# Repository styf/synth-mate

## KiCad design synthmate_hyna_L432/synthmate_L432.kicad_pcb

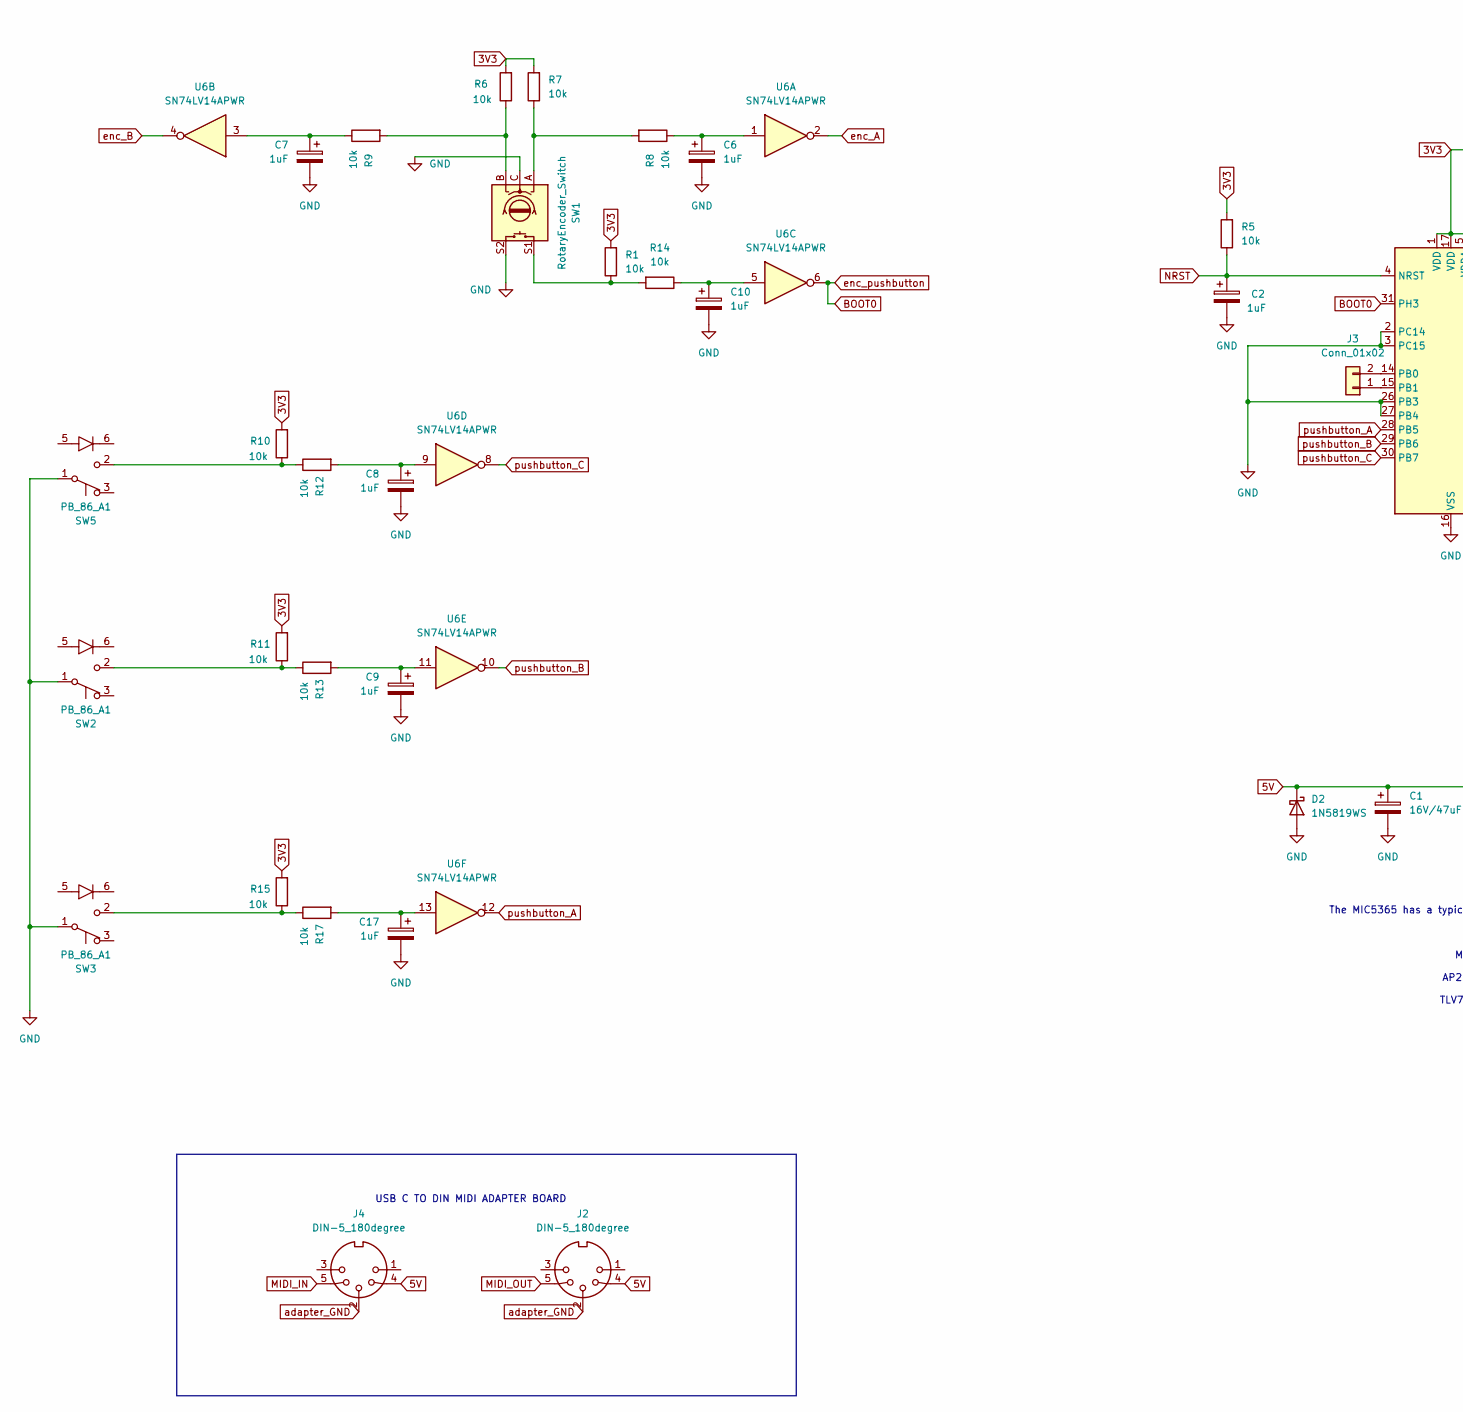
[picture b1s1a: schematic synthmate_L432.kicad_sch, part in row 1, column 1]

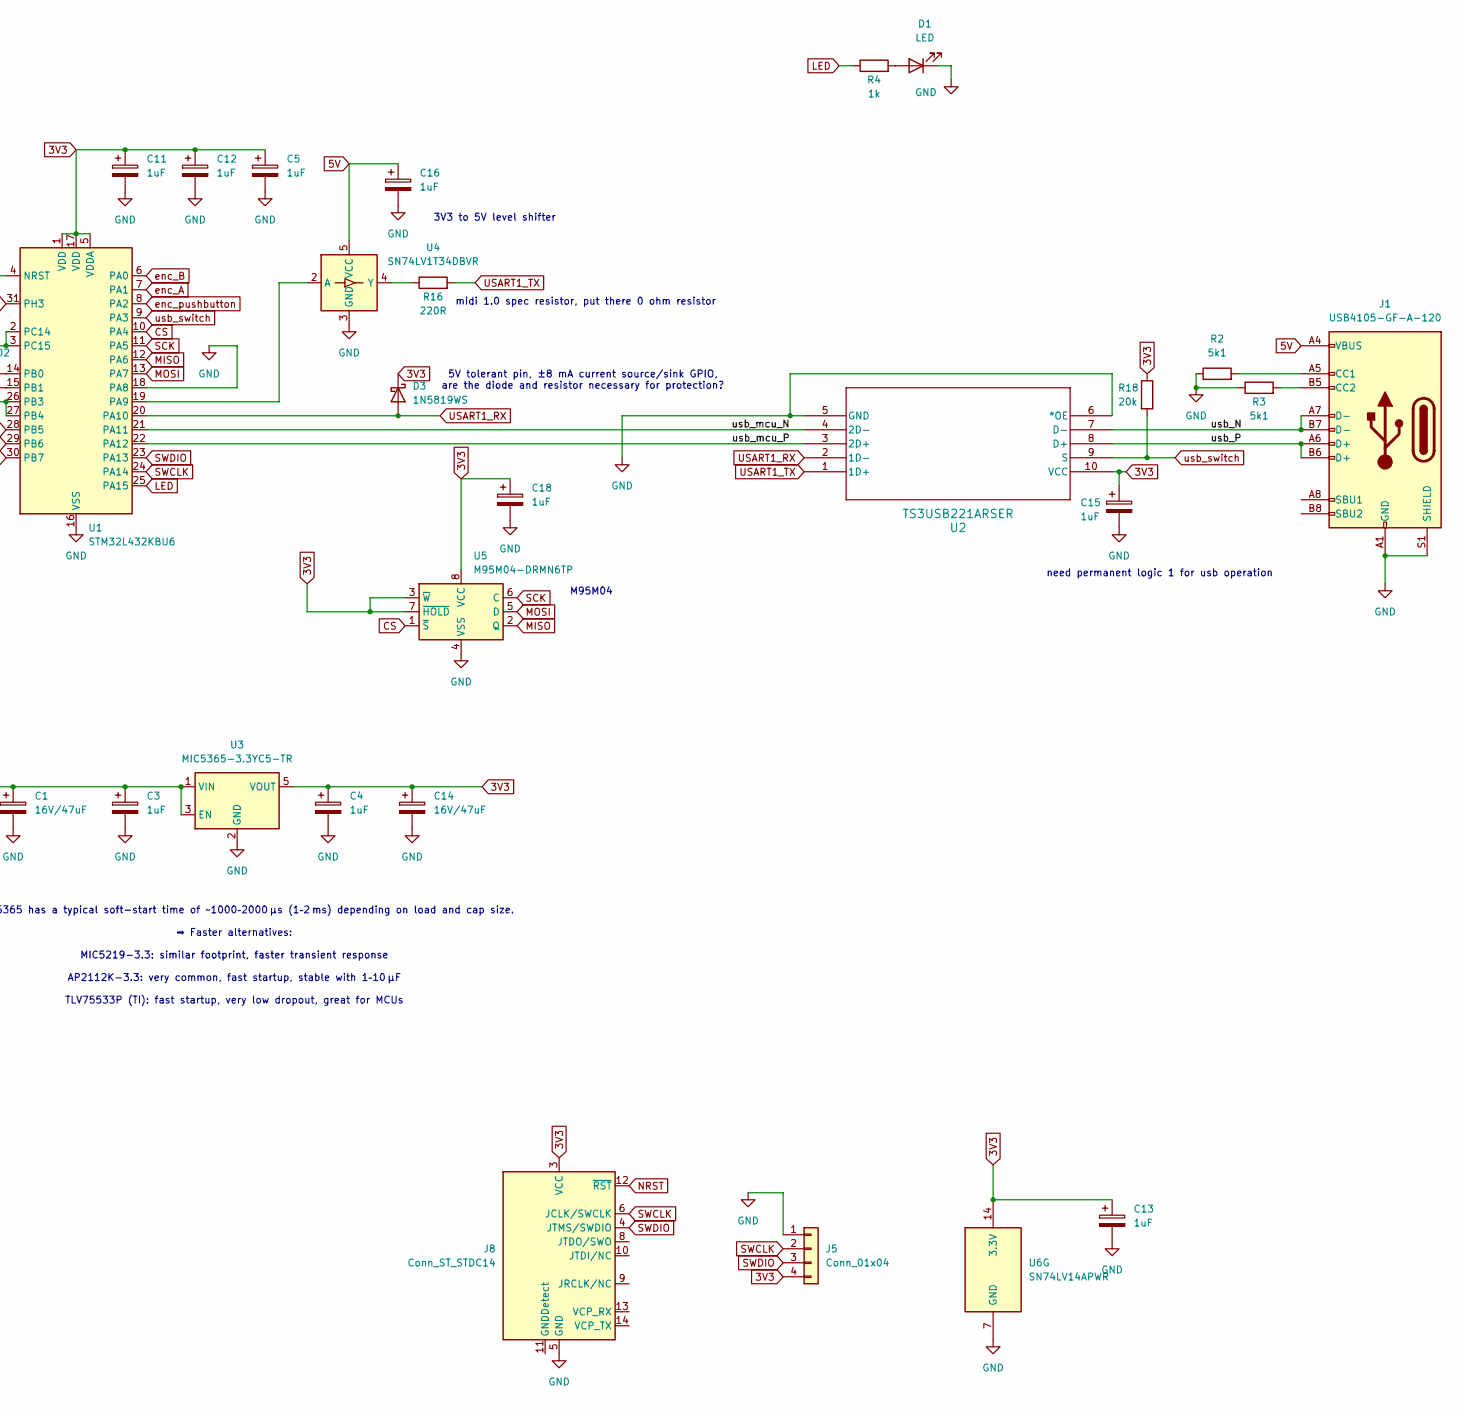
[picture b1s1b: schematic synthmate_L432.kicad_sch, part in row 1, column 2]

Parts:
C1, C14: 16V/47uF; C_1206_3216Metric
C2, C3, C4, C5, C6, C7, C8, C9, C10, C11, C12, C13, C15, C16, C17, C18: 1uF; C_0603_1608Metric
D1: LED; LED_0805_2012Metric_Pad1.15x1.40mm_HandSolder
D2, D3: 1N5819WS; D_SOD-323
J1: USB4105-GF-A-120; USB_C_Receptacle_GCT_USB4105-xx-A_16P_TopMnt_Horizontal
J2, J4: DIN-5_180degree
J3: Conn_01x02; PinHeader_1x02_P1.00mm_Vertical
J5: Conn_01x04; PinHeader_1x04_P2.54mm_Vertical
J8: Conn_ST_STDC14; PinHeader_2x07_P1.27mm_Vertical_SMD
R1, R5, R6, R7, R8, R9, R10, R11, R12, R13, R14, R15, R17: 10k; R_0603_1608Metric
R2, R3: 5k1; R_0603_1608Metric
R4: 1k; R_0603_1608Metric
R16: 220R; R_0603_1608Metric
R18: 20k; R_0603_1608Metric
SW1: RotaryEncoder_Switch; RotaryEncoder_Alps_EC11E-Switch_Vertical_H20mm
SW2, SW3, SW5: PB_86_A1; PB_86_A0
U1: STM32L432KBU6; QFN-32-1EP_5x5mm_P0.5mm_EP3.45x3.45mm
U2: TS3USB221ARSER; RSE10
U3: MIC5365-3.3YC5-TR; SOT-353_SC-70-5
U4: SN74LV1T34DBVR; SOT-23-5
U5: M95M04-DRMN6TP; SOIC-8_3.9x4.9mm_P1.27mm
U6: SN74LV14APWR; TSSOP-14_4.4x5mm_P0.65mm

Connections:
3V3: C4.1, C5.1, C11.1, C12.1, C13.1, C14.1, C15.1, C18.1, D3.1 (K), J5.4, J8.3 (VCC), R1.2, R5.2, R6.2, R7.2, R10.2, R11.2, R15.2, R18.1, U1.1 (VDD), U1.5 (VDDA), U1.17 (VDD), U2.10 (VCC), U3.5 (VOUT), U5.3 (~W), U5.7 (~HOLD), U5.8 (VCC), U6.14 (3.3V)
5V: C1.1, C3.1, C16.1, D2.1 (K), J1.A4 (VBUS), J1.A9 (VBUS), J1.B4 (VBUS), J1.B9 (VBUS), J2.4, J4.4, U3.1 (VIN), U3.3 (EN), U4.5 (VCC)
/usb_N: J1.A7 (D-), J1.B7 (D-), U2.7 (D-)
/usb_P: J1.A6 (D+), J1.B6 (D+), U2.8 (D+)
/usb_mcu_N: U1.21 (PA11), U2.4 (2D-)
/usb_mcu_P: U1.22 (PA12), U2.3 (2D+)
BOOT0: U1.8 (PA2), U1.31 (PH3), U6.6
CS: U1.10 (PA4), U5.1 (~S)
GND: C1.2, C2.2, C3.2, C4.2, C5.2, C6.2, C7.2, C8.2, C9.2, C10.2, C11.2, C12.2, C13.2, C14.2, C15.2, C16.2, C17.2, C18.2, D1.1 (K), D2.2 (A), J1.A1 (GND), J1.A12 (GND), J1.B1 (GND), J1.B12 (GND), J1.S1 (SHIELD), J5.1, J8.5 (GND), J8.7 (GND), R2.1, R3.1, SW1.C, SW1.S2, SW2.1 (B), SW3.1 (B), SW5.1 (B), U1.2 (PC14), U1.3 (PC15), U1.16 (VSS), U1.18 (PA8), U1.26 (PB3), U1.27 (PB4), U1.32 (VSS), U1.33 (VSS), U2.5 (GND), U2.6 (*OE), U3.2 (GND), U4.3 (GND), U5.4 (VSS), U6.7 (GND)
LED: R4.1, U1.25 (PA15)
MISO: U1.12 (PA6), U5.2 (Q)
MOSI: U1.13 (PA7), U5.5 (D)
NRST: C2.1, J8.12 (~RST), R5.1, U1.4 (NRST)
unnamed: C6.1, R8.1, U6.1
unnamed: C7.1, R9.1, U6.3
unnamed: C8.1, R12.2, U6.9
unnamed: C9.1, R13.2, U6.11
unnamed: C10.1, R14.1, U6.5
unnamed: C17.1, R17.2, U6.13
unnamed: D1.2 (A), R4.2
unnamed: J1.A5 (CC1), R2.2
unnamed: J1.B5 (CC2), R3.2
unnamed: J2.2, J4.2
unnamed: J3.1, U1.15 (PB1)
unnamed: J3.2, U1.14 (PB0)
unnamed: R1.1, R14.2, SW1.S1
unnamed: R6.1, R9.2, SW1.B
unnamed: R7.1, R8.2, SW1.A
unnamed: R11.1, R13.1, SW2.2 (C)
unnamed: R15.1, R17.1, SW3.2 (C)
unnamed: R10.1, R12.1, SW5.2 (C)
unnamed: U1.19 (PA9), U4.2 (A)
unnamed: R16.1, U4.4 (Y)
SCK: U1.11 (PA5), U5.6 (C)
SWCLK: J5.2, J8.6 (JCLK/SWCLK), U1.24 (PA14)
SWDIO: J5.3, J8.4 (JTMS/SWDIO), U1.23 (PA13)
USART1_RX: D3.2 (A), U1.20 (PA10), U2.2 (1D-)
USART1_TX: R16.2, U2.1 (1D+)
enc_A: U1.7 (PA1), U6.2
enc_B: U1.6 (PA0), U6.4
pushbutton_A: U1.28 (PB5), U6.12
pushbutton_B: U1.29 (PB6), U6.10
pushbutton_C: U1.30 (PB7), U6.8
usb_switch: R18.2, U1.9 (PA3), U2.9 (S)

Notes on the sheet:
The MIC5365 has a typical soft-start time of ~1000–2000 µs (1–2 ms) depending on load and cap size. ➡️ Faster alternatives: MIC5219-3.3: similar footprint, faster transient response AP2112K-3.3: very common, fast startup, stable with 1–10 µF TLV75533P (TI): fast startup, very low dropout, great for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
M95M04
5V tolerant pin, ±8 mA current source/sink GPIO, are the diode and resistor necessary for protection?
3V3 to 5V level shifter
need permanent logic 1 for usb operation
USB C TO DIN MIDI ADAPTER BOARD
midi 1.0 spec resistor, put there 0 ohm resistor

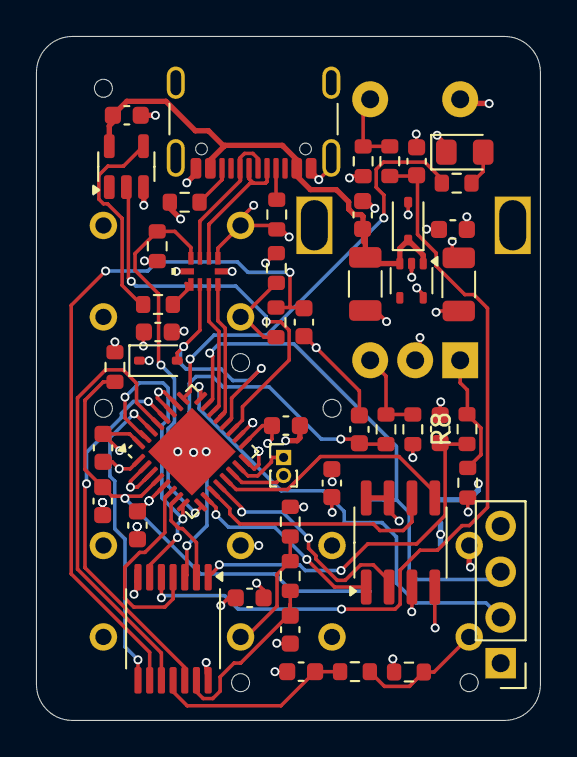
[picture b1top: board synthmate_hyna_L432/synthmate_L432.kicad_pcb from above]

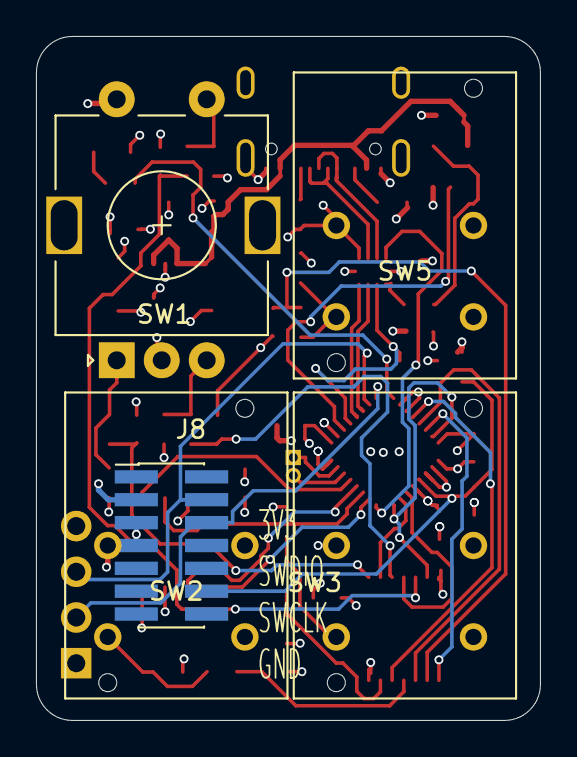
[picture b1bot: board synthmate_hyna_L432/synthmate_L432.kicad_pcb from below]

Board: 4 copper layers, 28.0 x 38.0 mm, 53 parts (5 on the bottom side), 43 nets.

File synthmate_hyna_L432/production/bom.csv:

Designator,Footprint,Quantity,Value,LCSC Part #
"C1, C14",1206,2,16V/47uF,
"C10, C11, C12, C13, C15, C16, C17, C18, C2, C3, C4, C5, C6, C7, C8, C9",0603,16,1uF,
D1,0805,1,LED,
"D2, D3",D_SOD-323,2,1N5819WS,
J1,USB_C_Receptacle_GCT_USB4105-xx-A_16P_TopMnt_Horizontal,1,USB4105-GF-A-120,
J3,PinHeader_1x02_P1.00mm_Vertical,1,Conn_01x02,
J5,PinHeader_1x04_P2.54mm_Vertical,1,Conn_01x04,
J8,PinHeader_2x07_P1.27mm_Vertical_SMD,1,Conn_ST_STDC14,
"R1, R10, R11, R12, R13, R14, R15, R17, R5, R6, R7, R8, R9",0603,13,10k,
R16,0603,1,220R,
R18,0603,1,20k,
"R2, R3",0603,2,5k1,
R4,0603,1,1k,
SW1,RotaryEncoder_Alps_EC11E-Switch_Vertical_H20mm,1,RotaryEncoder_Switch,
"SW2, SW3, SW5",PB_86_A0,3,PB_86_A1,
U1,QFN-32-1EP_5x5mm_P0.5mm_EP3.45x3.45mm,1,STM32L432KBU6,
U2,RSE10,1,TS3USB221ARSER,
U3,SOT-353_SC-70-5,1,MIC5365-3.3YC5-TR,
U4,SOT-23-5,1,SN74LV1T34DBVR,
U5,SOIC-8_3.9x4.9mm_P1.27mm,1,M95M04-DRMN6TP,
U6,TSSOP-14_4.4x5mm_P0.65mm,1,SN74LV14APWR,

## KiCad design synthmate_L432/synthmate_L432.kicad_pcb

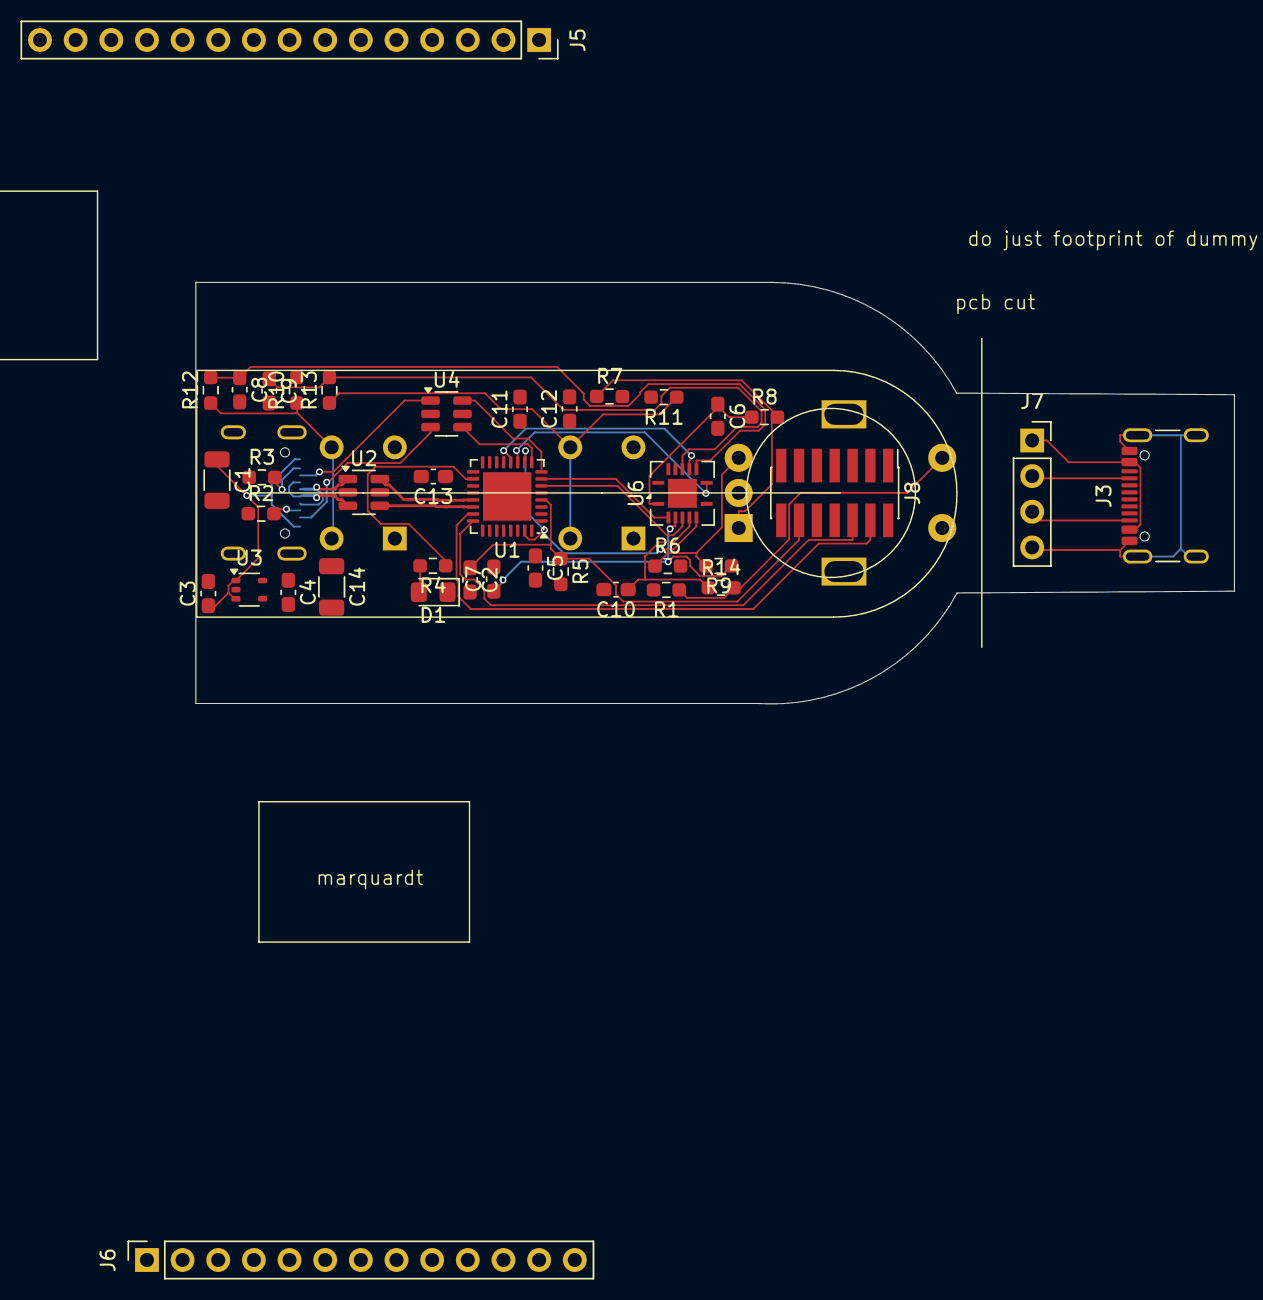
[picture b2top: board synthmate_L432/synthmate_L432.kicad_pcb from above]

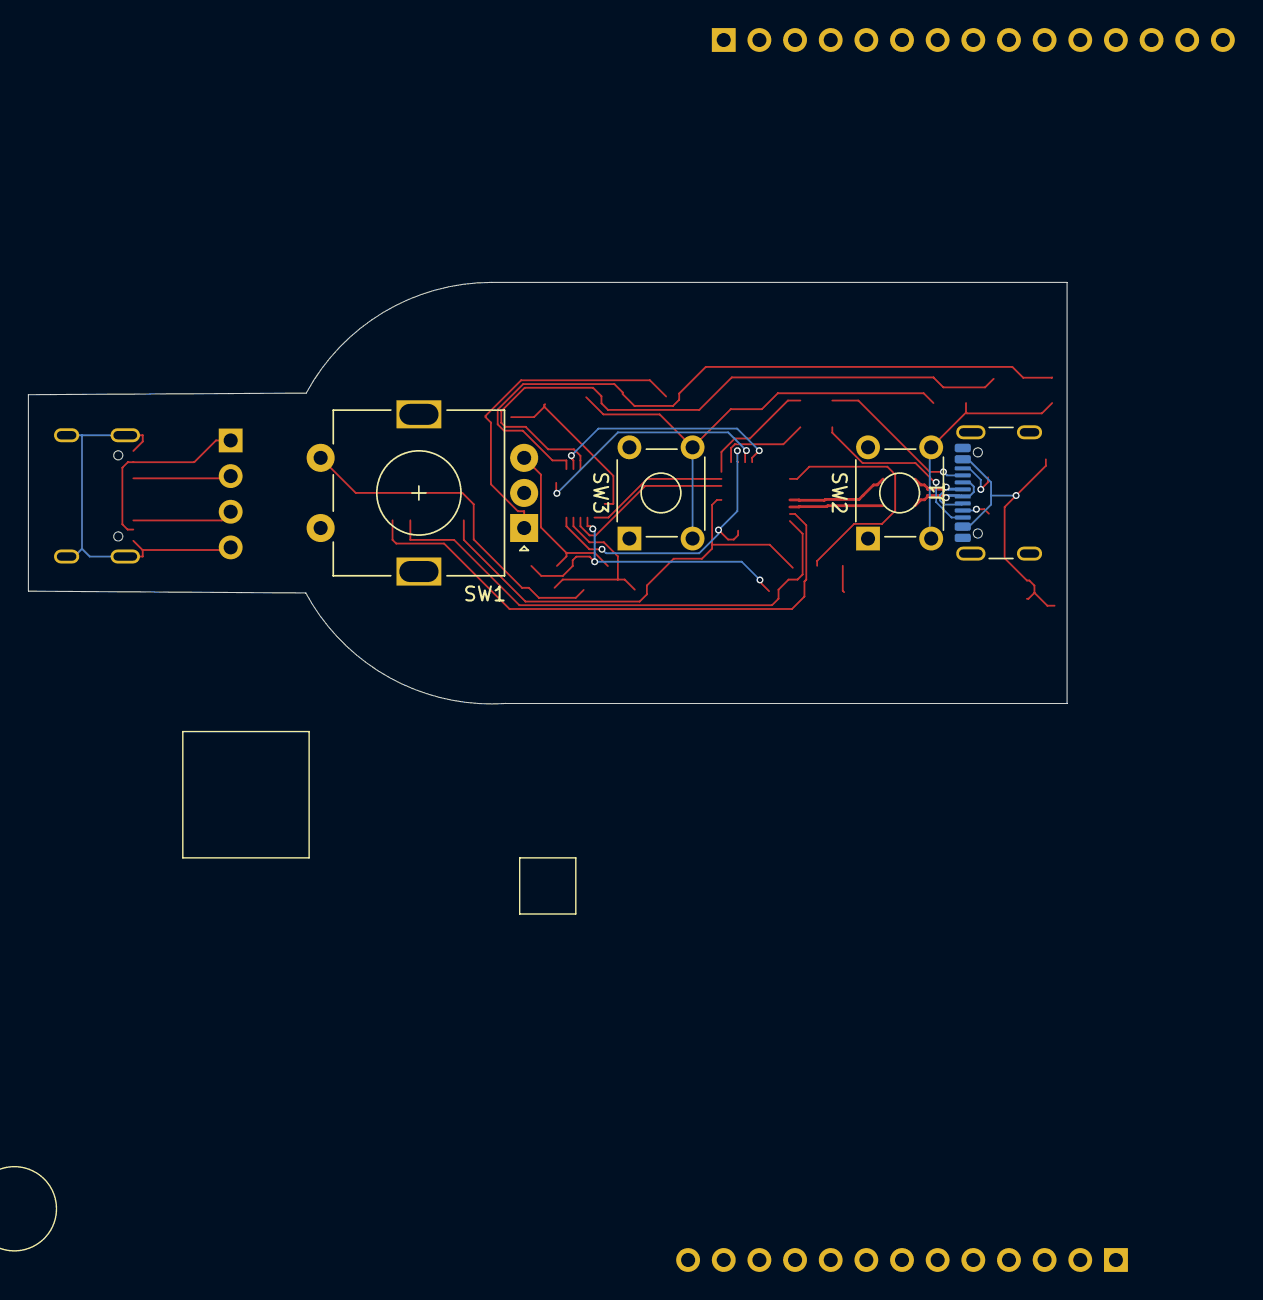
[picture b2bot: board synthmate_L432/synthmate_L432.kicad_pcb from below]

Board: 4 copper layers, 74.0 x 30.0 mm, 43 parts (4 on the bottom side), 37 nets.

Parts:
C1, C14: 16V/47uF; C_1206_3216Metric
C2, C5, C6, C7, C8, C9, C10, C11, C12: 100nF; C_0603_1608Metric_Pad1.08x0.95mm_HandSolder
C3, C4, C13: 1uF; C_0603_1608Metric_Pad1.08x0.95mm_HandSolder
D1: LED; LED_0805_2012Metric_Pad1.15x1.40mm_HandSolder
J1: USB_C_synthmate; USB_C_Receptacle_GCT_USB4105-xx-A_16P_TopMnt_Horizontal
J3: USB_C_connector_board; USB_C_Receptacle_GCT_USB4105-xx-A_16P_TopMnt_Horizontal
J5: Conn_01x16; PinSocket_1x15_P2.54mm_Vertical
J6: Conn_01x13; PinSocket_1x13_P2.54mm_Vertical
J7: Conn_01x04; PinSocket_1x04_P2.54mm_Vertical
J8: Conn_ST_STDC14; PinHeader_2x07_P1.27mm_Vertical_SMD
R1, R5, R6, R7, R8, R9, R10, R11, R12, R13, R14: 10k; R_0603_1608Metric_Pad0.98x0.95mm_HandSolder
R2, R3: 5k1; R_0603_1608Metric_Pad0.98x0.95mm_HandSolder
R4: 1k; R_0603_1608Metric_Pad0.98x0.95mm_HandSolder
SW1: RotaryEncoder_Switch; RotaryEncoder_Alps_EC11E-Switch_Vertical_H20mm
SW2, SW3: SW_Push; SW_TH_Tactile_Omron_B3F-10xx
U1: STM32L432KCUx; QFN-32-1EP_5x5mm_P0.5mm_EP3.45x3.45mm
U2, U4: USBLC6-2SC6; SOT-23-6
U3: MIC5365-1.0YC5; SOT-353_SC-70-5
U6: 74LV14; Texas_S-PVQFN-N14

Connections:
3V3: C4.1, C5.1, C11.1, C12.1, C13.1, C14.1, J8.3 (VCC), R1.2, R5.2, R6.2, R7.2, R10.2, R11.2, U1.1 (VDD), U1.5 (VDDA), U1.17 (VDD), U2.5 (VBUS), U3.5 (VOUT), U4.5 (VBUS), U6.14 (3.3V)
5V: C1.1, C3.1, J1.A4 (VBUS), J1.A9 (VBUS), J1.B4 (VBUS), J1.B9 (VBUS), U3.1 (VIN), U3.3 (EN)
/usb+: U1.22 (PA12), U2.4 (I/O2)
/usb-: U1.21 (PA11), U2.6 (I/O1)
/usb_N: J1.A7 (D-), J1.B7 (D-), U2.1 (I/O1)
/usb_P: J1.A6 (D+), J1.B6 (D+), U2.3 (I/O2)
BOOT0: U1.10 (PA4), U1.31 (PH3), U6.6
GND: C1.2, C2.2, C3.2, C4.2, C5.2, C6.2, C7.2, C8.2, C9.2, C10.2, C11.2, C12.2, C13.2, C14.2, D1.1 (K), J1.A1 (GND), J1.A12 (GND), J1.B1 (GND), J1.B12 (GND), J1.S1 (SHIELD), J8.5 (GND), J8.7 (GND), R2.1, R3.1, SW1.C, SW1.S2, SW2.1, SW3.1, U1.16 (VSS), U1.32 (VSS), U1.33 (VSS), U2.2 (GND), U3.2 (GND), U4.2 (GND), U6.7 (GND), U6.13
LED: R4.1, U1.18 (PA8)
LPUART_RX: U1.9 (PA3), U4.4 (I/O2)
LPUART_TX: U1.8 (PA2), U4.6 (I/O1)
NRST: C2.1, J8.12 (~RST), R5.1, U1.4 (NRST)
unnamed: C6.1, R8.1, U6.1
unnamed: C7.1, R9.1, U6.3
unnamed: C8.1, R12.2, U6.9
unnamed: C9.1, R13.2, U6.11
unnamed: C10.1, R14.1, U6.5
unnamed: D1.2 (A), R4.2
unnamed: J1.A5 (CC1), R2.2
unnamed: J1.B5 (CC2), R3.2
unnamed: J1.A8 (SBU1), U4.1 (I/O1)
unnamed: J1.B8 (SBU2), U4.3 (I/O2)
unnamed: R1.1, R14.2, SW1.S1
unnamed: R6.1, R9.2, SW1.B
unnamed: R7.1, R8.2, SW1.A
unnamed: R10.1, R12.1, SW2.2
unnamed: R11.1, R13.1, SW3.2
SWCLK: J8.6 (JCLK/SWCLK), U1.24 (PA14)
SWDIO: J8.4 (JTMS/SWDIO), U1.23 (PA13)
adaptor_5V: J3.A4 (VBUS), J3.A9 (VBUS), J3.B4 (VBUS), J3.B9 (VBUS), J7.1
adaptor_GND: J3.A1 (GND), J3.A12 (GND), J3.B1 (GND), J3.B12 (GND), J3.S1 (SHIELD), J7.4
adaptor_LPUART_RX: J3.A8 (SBU1), J7.2
adaptor_LPUART_TX: J3.B8 (SBU2), J7.3
enc_A: U1.7 (PA1), U6.2
enc_B: U1.6 (PA0), U6.4
pushbutton_A: U1.11 (PA5), U6.8
pushbutton_B: U1.12 (PA6), U6.10

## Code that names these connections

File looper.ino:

#include <Arduino.h>
#include <MIDI.h>

// --- Pin Definitions ---
#define PULLDOWN_PIN PA3
#define LED_PIN      PA15
#define BTN_RED      PB6   // REC / OVERDUB
#define BTN_GREEN    PB5   // PAUSE / RESUME
#define BTN_GREY     PB7   // STOP / CLEAR
#define BTN_ENC      PA2   // RESET TEMPO
#define ENC_A        PA1
#define ENC_B        PA0

// --- MIDI Setup ---
HardwareSerial SerialMIDI(PA10, PA9);
MIDI_CREATE_INSTANCE(HardwareSerial, SerialMIDI, MIDI);

// --- Looper Structures ---
typedef struct {
  uint32_t timestamp_ms;
  uint8_t pitch;
  uint8_t velocity;
  uint8_t channel;
} note_event_struct;

note_event_struct note_loop_buffer[512]; 
int noteMap[128]; 

// --- State Variables ---
int looper_state = 0; // 0:STOP, 1:REC, 2:PLAY, 3:HOLD, 4:OVERDUB
bool isPaused = false;
float tempo_factor = 1.0;

int note_event_count = 0;
int playback_index = 0;
uint32_t loop_length_ms = 0;
unsigned long loop_start_time = 0;
unsigned long playback_start_time = 0;
unsigned long time_paused = 0;
unsigned long pause_stamp = 0; // Fixed: Added declaration

volatile int Encoder = 0;
volatile int currentStateA;
volatile int previousStateA;

int lastBtnRed = LOW, lastBtnGreen = LOW, lastBtnGrey = LOW, lastBtnEnc = LOW;

// --- Encoder Interrupt ---
void readEnc() {
  currentStateA = digitalRead(ENC_A);
  if (currentStateA != previousStateA) {
    if (digitalRead(ENC_B) != currentStateA) {
      Encoder--;
      tempo_factor *= 0.98;
    } else {
      Encoder++;
      tempo_factor *= 1.02;
    }
  }
  previousStateA = currentStateA;
}

// --- MIDI Handlers ---
void handleNoteOn(byte channel, byte pitch, byte velocity) {
  MIDI.sendNoteOn(pitch, velocity, channel); 

  if (looper_state == 3) {
    looper_state = 1;
    loop_start_time = millis();
  }

  if ((looper_state == 1 || looper_state == 4) && note_event_count < 512) {
    uint32_t ts;
    if (looper_state == 1) ts = millis() - loop_start_time;
    else ts = (millis() - playback_start_time - time_paused) * tempo_factor;
    
    note_loop_buffer[note_event_count] = {ts, pitch, velocity, channel};
    note_event_count++;
  }
}

void handleNoteOff(byte channel, byte pitch, byte velocity) {
  MIDI.sendNoteOff(pitch, velocity, channel); 

  if ((looper_state == 1 || looper_state == 4) && note_event_count < 512) {
    uint32_t ts;
    if (looper_state == 1) ts = millis() - loop_start_time;
    else ts = (millis() - playback_start_time - time_paused) * tempo_factor;
    
    note_loop_buffer[note_event_count] = {ts, pitch, 0, channel};
    note_event_count++;
  }
}

void hangingOff() {
  for (int i = 0; i < 128; i++) {
    if (noteMap[i] > 0) {
      MIDI.sendNoteOff(i, 0, 1);
      noteMap[i] = 0;
    }
  }
}

void playNoteLooper() {
  if ((looper_state != 2 && looper_state != 4) || isPaused) return;

  unsigned long current_time_in_loop = millis() - playback_start_time - time_paused;
  uint32_t scaled_loop_length = (uint32_t)((float)loop_length_ms / tempo_factor);

  // Restart Loop
  if (current_time_in_loop >= scaled_loop_length) {
    hangingOff();
    playback_start_time = millis();
    playback_index = 0;
    time_paused = 0;
    return;
  }

  while (playback_index < note_event_count) {
    note_event_struct e = note_loop_buffer[playback_index];
    uint32_t scaled_ts = (uint32_t)((float)e.timestamp_ms / tempo_factor);

    if (current_time_in_loop >= scaled_ts) {
      if (e.velocity > 0) {
        MIDI.sendNoteOn(e.pitch, e.velocity, e.channel);
        noteMap[e.pitch] = e.velocity;
      } else {
        MIDI.sendNoteOff(e.pitch, 0, e.channel);
        noteMap[e.pitch] = 0;
      }
      playback_index++;
    } else {
      break;
    }
  }
}

void setup() {
  // Pull down PA3 immediately
  pinMode(PULLDOWN_PIN, OUTPUT);
  digitalWrite(PULLDOWN_PIN, LOW);

  pinMode(LED_PIN, OUTPUT);
  pinMode(BTN_RED, INPUT);
  pinMode(BTN_GREEN, INPUT);
  pinMode(BTN_GREY, INPUT);
  pinMode(BTN_ENC, INPUT);
  pinMode(ENC_A, INPUT);
  pinMode(ENC_B, INPUT);

  SerialMIDI.begin(31250);
  MIDI.begin(MIDI_CHANNEL_OMNI);
  MIDI.setHandleNoteOn(handleNoteOn);
  MIDI.setHandleNoteOff(handleNoteOff);

  previousStateA = digitalRead(ENC_A);
  attachInterrupt(digitalPinToInterrupt(ENC_A), readEnc, CHANGE);
}

void loop() {
  MIDI.read();
  
  int btnRed = digitalRead(BTN_RED);
  int btnGreen = digitalRead(BTN_GREEN);
  int btnGrey = digitalRead(BTN_GREY);
  int btnEnc = digitalRead(BTN_ENC);

  // --- RED: REC / PLAY / OVERDUB ---
  if (btnRed == HIGH && lastBtnRed == LOW) {
    if (looper_state == 0) {
      looper_state = 3; // Wait for note
      note_event_count = 0;
    } else if (looper_state == 1) {
      // Transition from REC to PLAY
      loop_length_ms = millis() - loop_start_time;
      hangingOff();         
      playback_index = 0;   
      time_paused = 0;      
      playback_start_time = millis(); // Loop starts NOW
      looper_state = 2;     
    } else if (looper_state == 2) {
      looper_state = 4; // Start Overdub
    } else if (looper_state == 4) {
      looper_state = 2; // Back to Play
    }
  }
  lastBtnRed = btnRed;

  // --- GREEN: PAUSE / RESUME ---
  if (btnGreen == HIGH && lastBtnGreen == LOW) {
    if (looper_state == 2 || looper_state == 4) {
      isPaused = !isPaused;
      if (isPaused) {
        hangingOff();
        pause_stamp = millis(); 
      } else {
        time_paused += (millis() - pause_stamp);
      }
    }
  }
  lastBtnGreen = btnGreen;

  // --- GREY: CLEAR ---
  if (btnGrey == HIGH && lastBtnGrey == LOW) {
    looper_state = 0;
    hangingOff();
    note_event_count = 0;
    playback_index = 0;
    time_paused = 0;
    tempo_factor = 1.0;
  }
  lastBtnGrey = btnGrey;

  // --- ENC BTN: RESET ---
  if (btnEnc == HIGH && lastBtnEnc == LOW) {
    tempo_factor = 1.0;
    Encoder = 0;
  }
  lastBtnEnc = btnEnc;

  playNoteLooper();

  // LED Visuals
  if (looper_state == 1 || looper_state == 3) digitalWrite(LED_PIN, (millis() % 200 < 100)); // Fast Blink
  else if (looper_state == 4) digitalWrite(LED_PIN, (millis() % 600 < 300)); // Slow Blink
  else if (looper_state == 2 && !isPaused) digitalWrite(LED_PIN, HIGH); // Solid Play
  else digitalWrite(LED_PIN, LOW);
}

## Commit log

2020-06-02 eachkey, first key freerunning
2020-06-02 switch nrpn/ctlin
2020-06-02 enum modcontrol
2020-06-04 ectl_struct
2020-06-04 ctl_struct
2020-06-04 _change
2020-06-05 MW repair
2020-06-05 PB up down
2020-06-05 AUTOMATION + MODCONTROL, nastrel rate scaling
2025-06-03 kicad_repository
2025-06-04 pin headers, led, usart1
2025-06-16 pcb_v1
2025-06-18 switch to 4 layers, top layer signals routed
2025-06-21 added debounce
2025-06-21 fur hynek
2025-06-21 pcb outline
2025-06-26 74LV14 / TPD4E02B04DQA
    changed schmitt to 74LV14 and ESD to TPD4E02B04DQA
2025-06-26 moved smd to bottom side, changed back to eusblc6
2025-06-26 gitignore
2025-07-29 pcb_V0
2025-08-01 added analog mux on main board nd adapter board
2025-08-01 cleanup
2025-08-04 adapter board rx/tx switching logic
2025-08-09 adapter board cleanup, uart IO protection added
2025-10-13 V2_gerber
2025-10-13 V2_GERBER
    S
2025-11-01 gerber_v2
2025-12-17 Revert "gerber_v2"
    This reverts commit a36cd725a38217f085e25e19cc21183ca66f7b8c.
2025-12-29 before autorouter, locked footprints and usb
2025-12-29 naming cleanup
2026-01-23 23_1
2026-01-29 added LICENSE, looper, automation
2026-01-29 stress test with 4mhz config
2026-01-31 stress test with HSI 1 MHz
